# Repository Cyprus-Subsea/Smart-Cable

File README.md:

# Smart-Cable
Smart Cable is a cable assembly with a modular pressure tolerant electronics circuit embedded inline a cable assembly. It was deigned to be able to take care of most sensor integration needs such as voltage regulation, protocol translation, data processing, storage and many more which usually requires many months of engineering effort. The circuit consists of a base plate with the right connections to connect any variation of modules. the modules consist of processor module, protocol modules (RS-323, 485, 422, Ethernet, USB, CAN-bus) , power module and a variety of miscellaneous modules (ADC, memory, Real-time clock, etc.)

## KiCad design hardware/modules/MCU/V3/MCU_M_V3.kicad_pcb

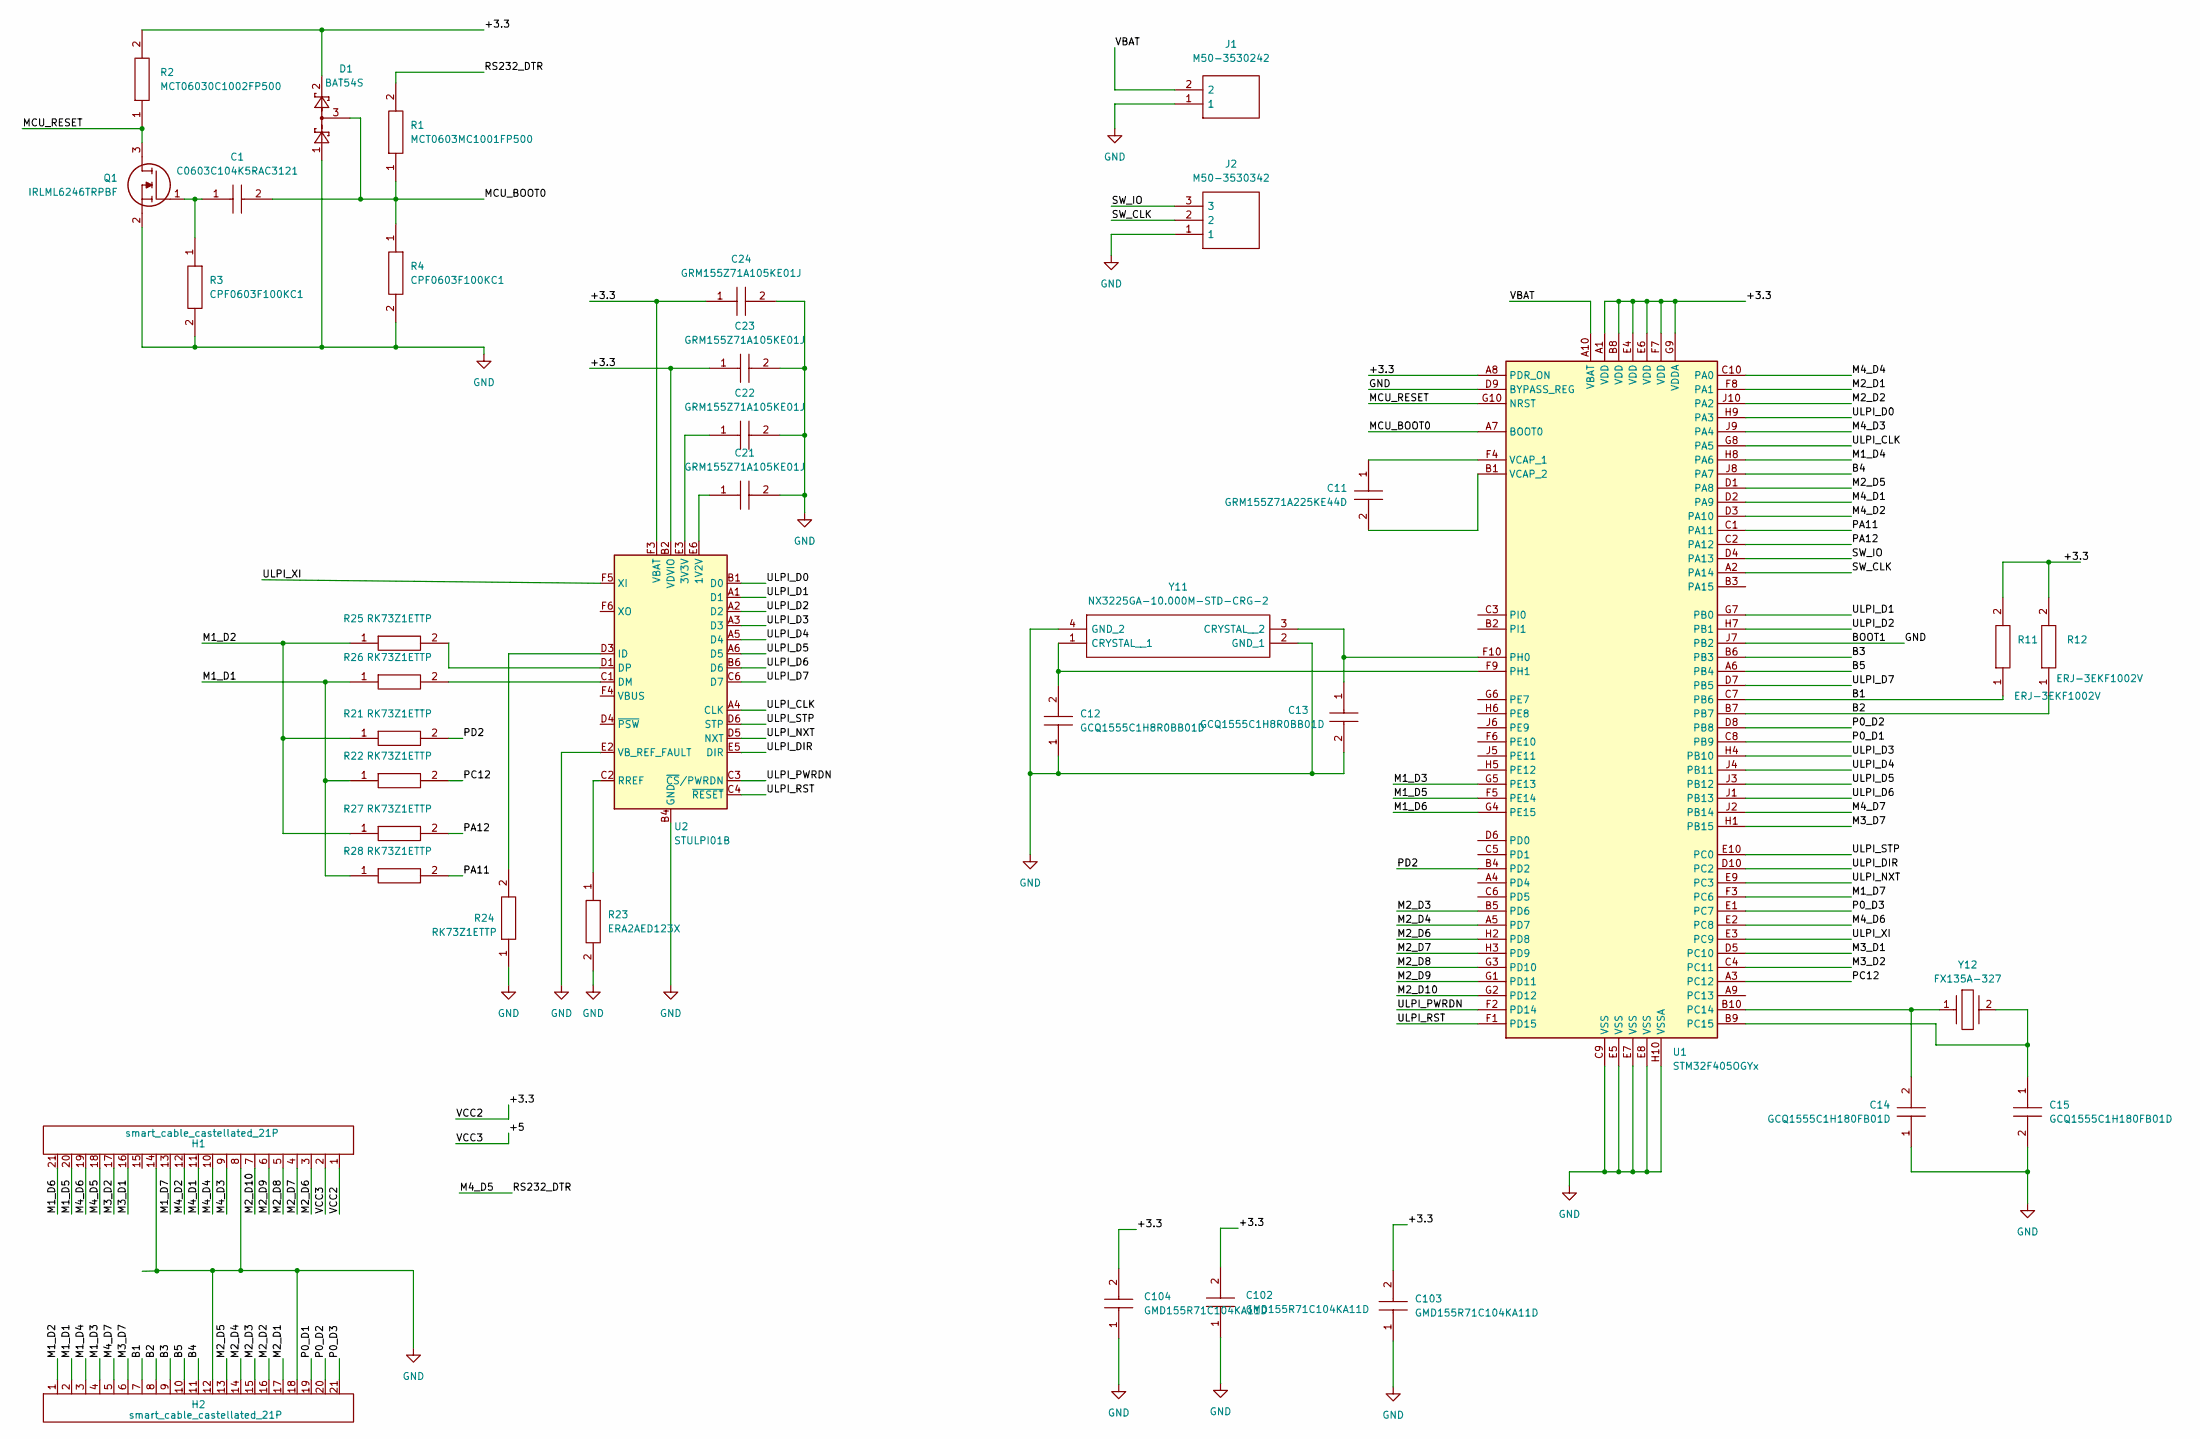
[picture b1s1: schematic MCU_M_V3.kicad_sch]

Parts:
C1: C0603C104K5RAC3121; CAPC1608X95N; Manufacturer_Part_Number C0603C104K5RAC3121; Mouser Part Number 80-C603C104K5RAC3121
C11: GRM155Z71A225KE44D; CAPC1005X55N; Manufacturer_Part_Number GRM155Z71A225KE44D; Mouser Part Number 81-GRM155Z71A225KE4D
C12, C13: GCQ1555C1H8R0BB01D; CAPC1005X55N; Manufacturer_Part_Number GCQ1555C1H8R0BB01D; Mouser Part Number 81-GCQ1555C1H8R0BB1D
C14, C15: GCQ1555C1H180FB01D; CAPC1005X55N; Manufacturer_Part_Number GCQ1555C1H180FB01D; Mouser Part Number 81-GCQ1555C1H180FB1D
C21, C22, C23, C24: GRM155Z71A105KE01J; CAPC1005X55N; Manufacturer_Part_Number GRM155Z71A105KE01J; Mouser Part Number 81-GRM155Z71A105KE1J
C102, C103, C104: GMD155R71C104KA11D; CAPC1005X55N; Manufacturer_Part_Number GMD155R71C104KA11D; Mouser Part Number 81-GMD155R71C104KA1D
D1: BAT54S; SOT-23
H1, H2: smart_cable_castellated_21P; smart_cable_castellated_21p
J1: M50-3530242; HDRV2W40P0X127_1X2_254X210X420P; Manufacturer_Part_Number M50-3530242; Mouser Part Number 855-M50-3530242
J2: M50-3530342; HDRV3W40P0X127_1X3_381X210X430P; Manufacturer_Part_Number M50-3530342; Mouser Part Number 855-M50-3530342
Q1: IRLML6246TRPBF; SOT95P237X112-3N; Manufacturer_Part_Number IRLML6246TRPBF; Mouser Part Number 942-IRLML6246TRPBF
R1: MCT0603MC1001FP500; RESC1608X55N; Manufacturer_Part_Number MCT0603MC1001FP500; Mouser Part Number 594-MCT0603MC1001FP5
R2: MCT06030C1002FP500; RESC1608X55N; Manufacturer_Part_Number MCT06030C1002FP500; Mouser Part Number 594-MCT06030C1002FP5
R3, R4: CPF0603F100KC1; RESC1608X55N; Manufacturer_Part_Number CPF0603F100KC1; Mouser Part Number 279-CPF0603F100KC1
R11, R12: ERJ-3EKF1002V; ERJ3EK_(0603); Manufacturer_Part_Number ERJ-3EKF1002V; Mouser Part Number 667-ERJ-3EKF1002V
R21, R22, R24, R25, R26, R27, R28: RK73Z1ETTP; RESC1005X40N; Manufacturer_Part_Number RK73Z1ETTP; Mouser Part Number 660-RK73Z1ETTP
R23: ERA2AED123X; ERA2AED122X; Manufacturer_Part_Number ERA2AED123X
U1: STM32F405OGYx; ST_WLCSP-90_Die413
U2: STULPI01B; ST_uTFBGA-36_3.6x3.6mm_Layout6x6_P0.5mm
Y11: NX3225GA-10.000M-STD-CRG-2; NX3225GA10000MSTDCRG2; Manufacturer_Part_Number NX3225GA-10.000M-STD-CRG-2; Mouser Part Number 344-NX3225GA10MSTRG2
Y12: FX135A-327; FX135A327; Manufacturer_Part_Number FX135A-327

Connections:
/+3.3: C23.1, C24.1, C102.2, C103.2, C104.2, D1.2, H1.1, R2.2, R11.2, R12.2, U1.A1 (VDD), U1.A8 (PDR_ON), U1.B8 (VDD), U1.E4 (VDD), U1.E6 (VDD), U1.F7 (VDD), U1.G9 (VDDA), U2.B2 (VDVIO), U2.B3 (VDVIO), U2.B5 (VDVIO), U2.F3 (VBAT)
/+5: H1.2
/B1: H2.7, R11.1, U1.C7 (PB6)
/B2: H2.8, R12.1, U1.B7
/B3: H2.9, U1.B6 (PB3)
/B4: H2.11, U1.J8 (PA7)
/B5: H2.10, U1.A6 (PB4)
/M1_D1: H2.2, R22.1, R26.1, R28.1
/M1_D2: H2.1, R21.1, R25.1, R27.1
/M1_D3: H2.4, U1.G5 (PE13)
/M1_D4: H2.3, U1.H8 (PA6)
/M1_D5: H1.20, U1.F5 (PE14)
/M1_D6: H1.21, U1.G4 (PE15)
/M1_D7: H1.13, U1.F3 (PC6)
/M2_D1: H2.17, U1.F8 (PA1)
/M2_D2: H2.16, U1.J10 (PA2)
/M2_D3: H2.15, U1.B5 (PD6)
/M2_D4: H2.14, U1.A5 (PD7)
/M2_D5: H2.13, U1.D1 (PA8)
/M2_D6: H1.3, U1.H2 (PD8)
/M2_D7: H1.4, U1.H3 (PD9)
/M2_D8: H1.5, U1.G3 (PD10)
/M2_D9: H1.6, U1.G1 (PD11)
/M2_D10: H1.7, U1.G2 (PD12)
/M3_D1: H1.16, U1.D5 (PC10)
/M3_D2: H1.17, U1.C4 (PC11)
/M3_D7: H2.6, U1.H1 (PB15)
/M4_D1: H1.11, U1.D2 (PA9)
/M4_D2: H1.12, U1.D3 (PA10)
/M4_D3: H1.9, U1.J9 (PA4)
/M4_D4: H1.10, U1.C10 (PA0)
/M4_D5: H1.18, R1.2
/M4_D6: H1.19, U1.E2 (PC8)
/M4_D7: H2.5, U1.J2 (PB14)
/MCU_BOOT0: C1.2, D1.3, R1.1, R4.1, U1.A7 (BOOT0)
/MCU_RESET: Q1.3, R2.1, U1.G10 (NRST)
/P0_D1: H2.19, U1.C8 (PB9)
/P0_D2: H2.20, U1.D8 (PB8)
/P0_D3: H2.21, U1.E1 (PC7)
/PA11: R28.2, U1.C1 (PA11)
/PA12: R27.2, U1.C2 (PA12)
/PC12: R22.2, U1.A3 (PC12)
/PD2: R21.2, U1.B4 (PD2)
/SW_CLK: J2.2, U1.A2 (PA14)
/SW_IO: J2.3, U1.D4 (PA13)
/ULPI_CLK: U1.G8 (PA5), U2.A4 (CLK)
/ULPI_D0: U1.H9 (PA3), U2.B1 (D0)
/ULPI_D1: U1.G7 (PB0), U2.A1 (D1)
/ULPI_D2: U1.H7 (PB1), U2.A2 (D2)
/ULPI_D3: U1.H4 (PB10), U2.A3 (D3)
/ULPI_D4: U1.J4 (PB11), U2.A5 (D4)
/ULPI_D5: U1.J3 (PB12), U2.A6 (D5)
/ULPI_D6: U1.J1 (PB13), U2.B6 (D6)
/ULPI_D7: U1.D7 (PB5), U2.C6 (D7)
/ULPI_DIR: U1.D10 (PC2), U2.E5 (DIR)
/ULPI_NXT: U1.E9 (PC3), U2.D5 (NXT)
/ULPI_PWRDN: U1.F2 (PD14), U2.C3 (~CS/PWRDN)
/ULPI_RST: U1.F1 (PD15), U2.C4 (~RESET)
/ULPI_STP: U1.E10 (PC0), U2.D6 (STP)
/ULPI_XI: U1.E3 (PC9), U2.F5 (XI)
/VBAT: J1.2, U1.A10 (VBAT)
GND: C12.1, C13.2, C14.1, C15.2, C21.2, C22.2, C23.2, C24.2, C102.1, C103.1, C104.1, D1.1, H1.8, H1.14, H2.12, H2.18, J1.1, J2.1, Q1.2, R3.2, R4.2, R23.2, R24.1, U1.C9 (VSS), U1.D9 (BYPASS_REG), U1.E5 (VSS), U1.E7 (VSS), U1.E8 (VSS), U1.H10 (VSSA), U1.J7 (PB2), U2.B4 (GND), U2.C5 (GND), U2.D2 (GND), U2.E1 (GND), U2.E2 (VB_REF_FAULT), U2.E4 (GND), Y11.2 (GND_1), Y11.4 (GND_2)
unnamed: C1.1, Q1.1, R3.1
unnamed: C11.1, U1.F4 (VCAP_1)
unnamed: C11.2, U1.B1 (VCAP_2)
unnamed: C12.2, U1.F9 (PH1), Y11.1 (CRYSTAL__1)
unnamed: C13.1, U1.F10 (PH0), Y11.3 (CRYSTAL__2)
unnamed: C14.2, U1.B10 (PC14), Y12.1
unnamed: C15.1, U1.B9 (PC15), Y12.2
unnamed: C21.1, U2.E6 (1V2V)
unnamed: C22.1, U2.E3 (3V3V)
unnamed: R23.1, U2.C2 (RREF)
unnamed: R24.2, U2.D3 (ID)
unnamed: R25.2, U2.D1 (DP)
unnamed: R26.2, U2.C1 (DM)

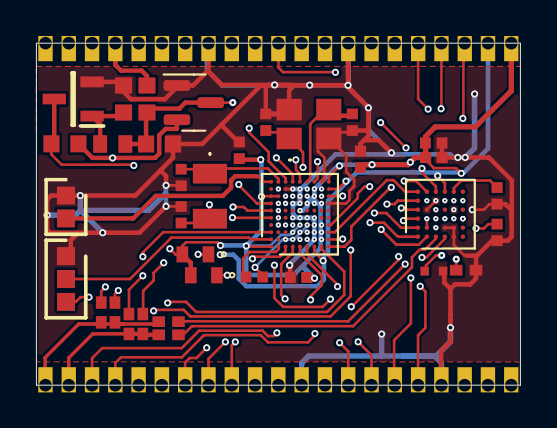
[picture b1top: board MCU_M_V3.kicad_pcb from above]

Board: 4 copper layers, 26.9 x 19.0 mm, 37 parts (0 on the bottom side), 74 nets.

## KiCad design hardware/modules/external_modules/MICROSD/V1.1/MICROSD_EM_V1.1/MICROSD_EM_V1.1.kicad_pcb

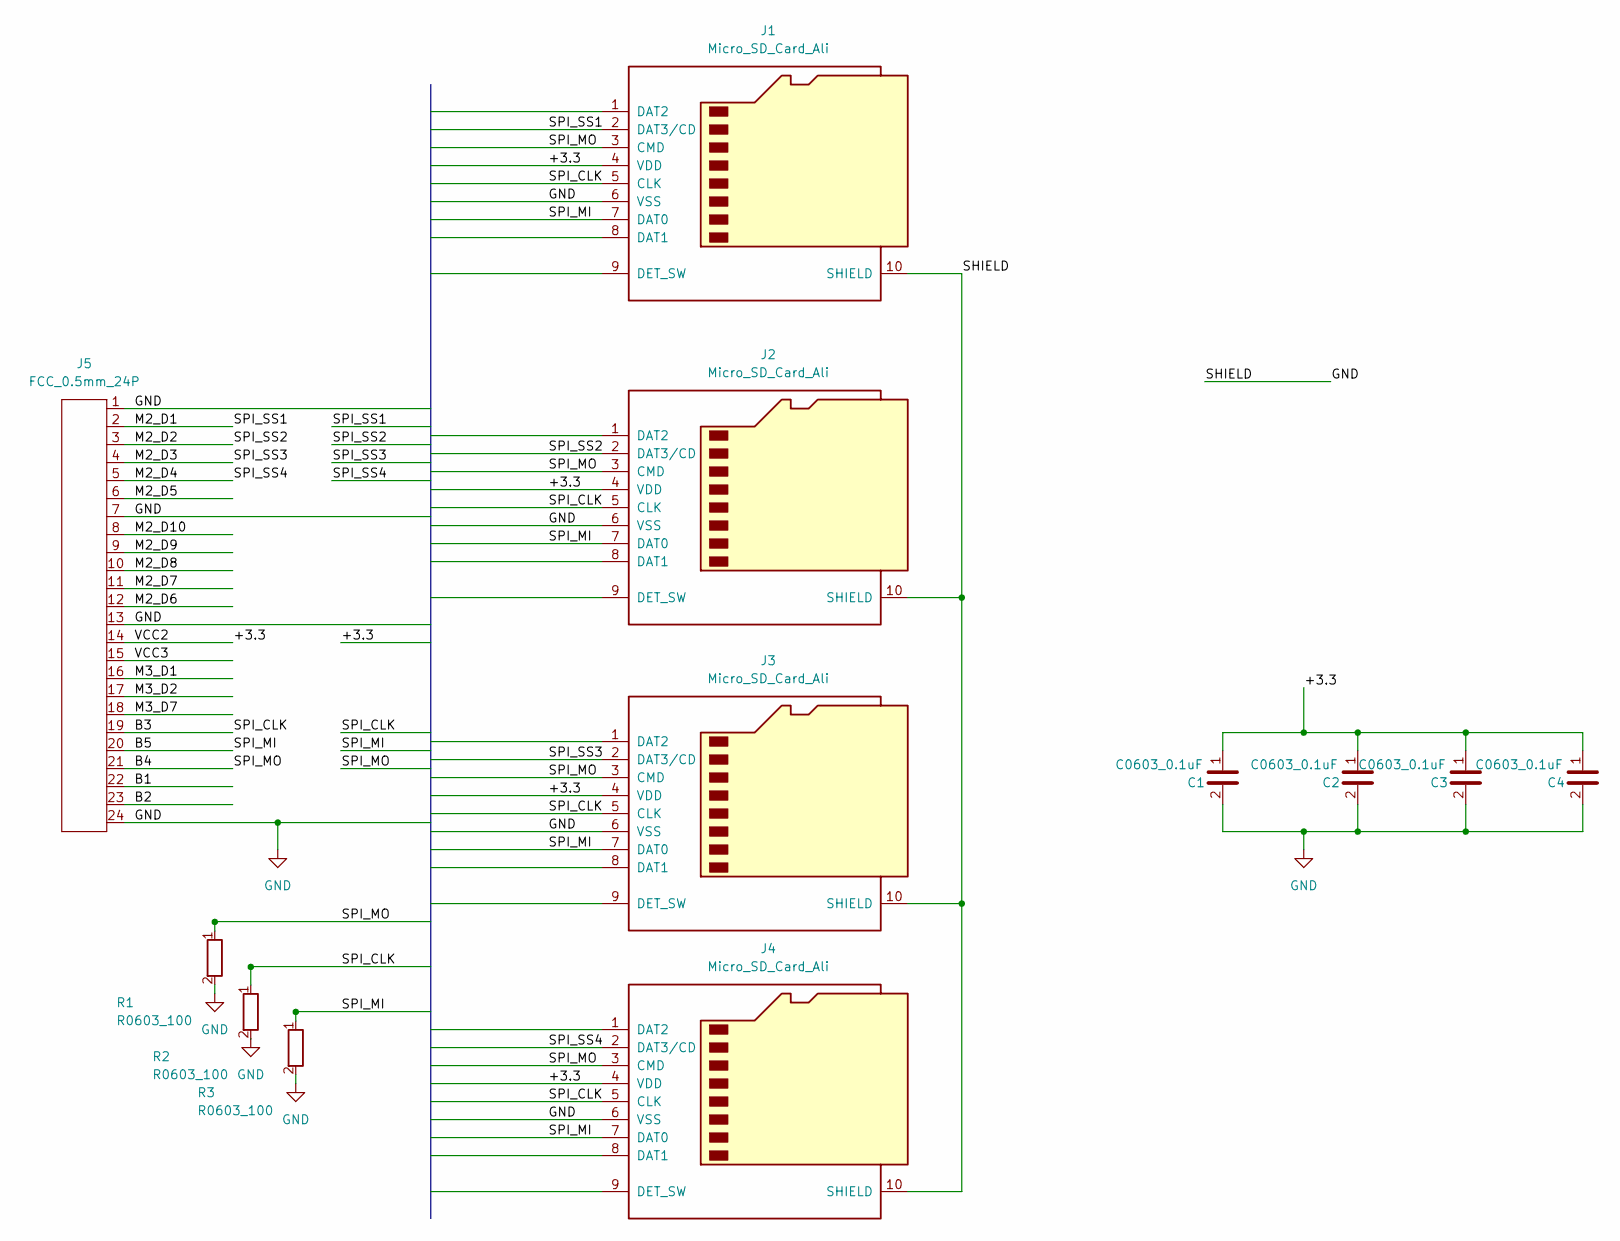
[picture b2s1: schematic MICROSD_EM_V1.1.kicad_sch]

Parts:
C1, C2, C3, C4: C0603_0.1uF; C_0603_1608Metric
J1, J2, J3, J4: Micro_SD_Card_Ali; MicroSD_ALI
J5: FCC_0.5mm_24P; FCC 0.5mm 24P
R1, R2, R3: R0603_100; R_0603_1608Metric

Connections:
/+3.3: C1.1, C2.1, C3.1, C4.1, J1.4 (VDD), J2.4 (VDD), J3.4 (VDD), J4.4 (VDD), J5.14
/B1: J5.22
/B2: J5.23
/B3: J1.5 (CLK), J2.5 (CLK), J3.5 (CLK), J4.5 (CLK), J5.19, R2.1
/B4: J1.3 (CMD), J2.3 (CMD), J3.3 (CMD), J4.3 (CMD), J5.21, R1.1
/B5: J1.7 (DAT0), J2.7 (DAT0), J3.7 (DAT0), J4.7 (DAT0), J5.20, R3.1
/M2_D1: J1.2 (DAT3/CD), J5.2
/M2_D2: J2.2 (DAT3/CD), J5.3
/M2_D3: J3.2 (DAT3/CD), J5.4
/M2_D4: J4.2 (DAT3/CD), J5.5
/M2_D5: J5.6
/M2_D6: J5.12
/M2_D7: J5.11
/M2_D8: J5.10
/M2_D9: J5.9
/M2_D10: J5.8
/M3_D1: J5.16
/M3_D2: J5.17
/M3_D7: J5.18
/VCC3: J5.15
GND: C1.2, C2.2, C3.2, C4.2, J1.6 (VSS), J1.10 (SHIELD), J2.6 (VSS), J2.10 (SHIELD), J3.6 (VSS), J3.10 (SHIELD), J4.6 (VSS), J4.10 (SHIELD), J5.1, J5.7, J5.13, J5.24, R1.2, R2.2, R3.2

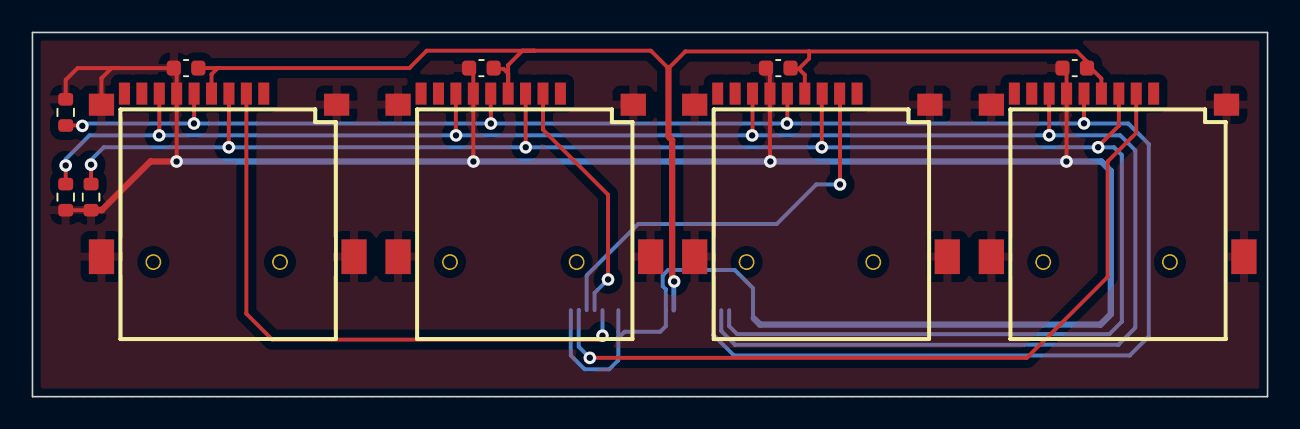
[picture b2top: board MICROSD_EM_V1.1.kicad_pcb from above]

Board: 2 copper layers, 78.0 x 23.0 mm, 12 parts (1 on the bottom side), 9 nets.

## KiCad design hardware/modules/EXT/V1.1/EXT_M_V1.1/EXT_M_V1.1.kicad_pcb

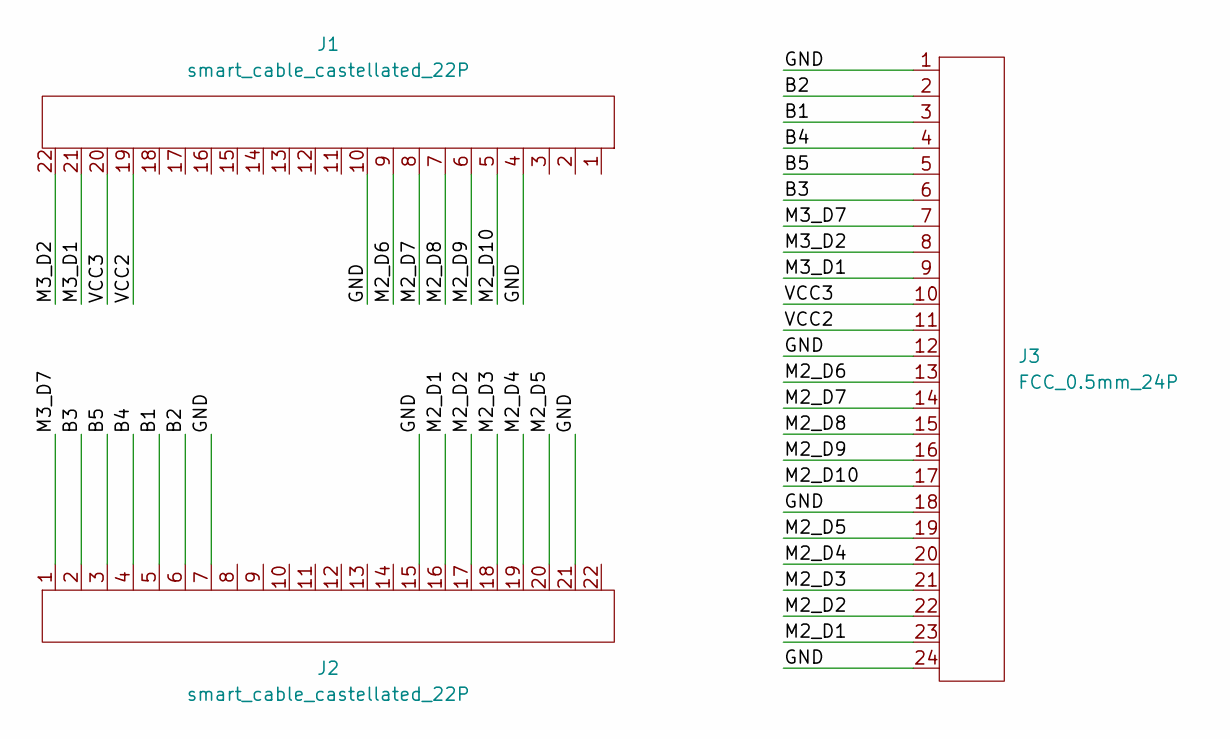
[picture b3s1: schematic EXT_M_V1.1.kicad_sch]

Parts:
J1, J2: smart_cable_castellated_22P; smart_cable_castellated_22p
J3: FCC_0.5mm_24P; FCC 0.5mm 24P

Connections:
/B1: J2.5, J3.3
/B2: J2.6, J3.2
/B3: J2.2, J3.6
/B4: J2.4, J3.4
/B5: J2.3, J3.5
/GND: J1.4, J1.10, J2.7, J2.15, J2.21, J3.1, J3.12, J3.18, J3.24
/M2_D1: J2.16, J3.23
/M2_D2: J2.17, J3.22
/M2_D3: J2.18, J3.21
/M2_D4: J2.19, J3.20
/M2_D5: J2.20, J3.19
/M2_D6: J1.9, J3.13
/M2_D7: J1.8, J3.14
/M2_D8: J1.7, J3.15
/M2_D9: J1.6, J3.16
/M2_D10: J1.5, J3.17
/M3_D1: J1.21, J3.9
/M3_D2: J1.22, J3.8
/M3_D7: J2.1, J3.7
/VCC2: J1.19, J3.11
/VCC3: J1.20, J3.10

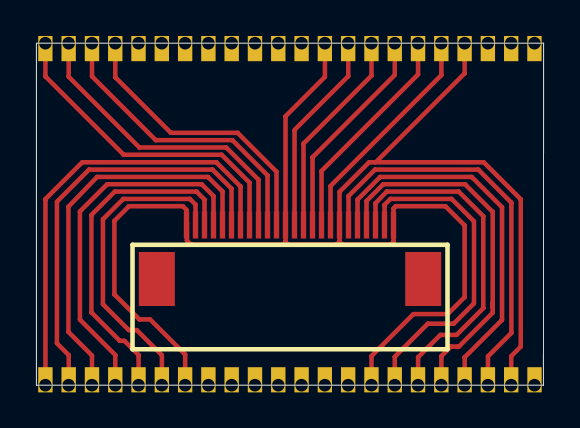
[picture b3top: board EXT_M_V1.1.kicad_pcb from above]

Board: 2 copper layers, 28.2 x 19.0 mm, 3 parts (0 on the bottom side), 21 nets.

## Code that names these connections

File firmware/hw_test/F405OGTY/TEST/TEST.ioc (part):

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Mcu.Name=STM32F405O(E-G)Yx
Mcu.Package=WLCSP90
Mcu.UserName=STM32F405OGYx
PA3.Mode=Host_HS
PA3.Signal=USB_OTG_HS_ULPI_D0
PA5.Mode=Host_HS
PA5.Signal=USB_OTG_HS_ULPI_CK
PB0.Mode=Host_HS
PB0.Signal=USB_OTG_HS_ULPI_D1
PB1.Mode=Host_HS
PB1.Signal=USB_OTG_HS_ULPI_D2
PB10.Mode=Host_HS
PB10.Signal=USB_OTG_HS_ULPI_D3
PB11.Mode=Host_HS
PB11.Signal=USB_OTG_HS_ULPI_D4
PB12.Mode=Host_HS
PB12.Signal=USB_OTG_HS_ULPI_D5
PB13.Mode=Host_HS
PB13.Signal=USB_OTG_HS_ULPI_D6
PB5.Mode=Host_HS
PB5.Signal=USB_OTG_HS_ULPI_D7
PC0.Mode=Host_HS
PC0.Signal=USB_OTG_HS_ULPI_STP
PC2.Mode=Host_HS
PC2.Signal=USB_OTG_HS_ULPI_DIR
PC3.Mode=Host_HS
PC3.Signal=USB_OTG_HS_ULPI_NXT
PC9.Mode=Clock-out-2
PC9.Signal=RCC_MCO_2
PH0-OSC_IN.Mode=HSE-External-Oscillator
PH0-OSC_IN.Signal=RCC_OSC_IN
PH1-OSC_OUT.Mode=HSE-External-Oscillator
PH1-OSC_OUT.Signal=RCC_OSC_OUT
RCC.HSE_VALUE=10000000
RCC.SYSCLKFreq_VALUE=100000000
RCC.SYSCLKSource=RCC_SYSCLKSOURCE_PLLCLK
board=custom

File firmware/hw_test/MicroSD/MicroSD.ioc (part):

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Mcu.Name=STM32F405RGTx
Mcu.Package=LQFP64
Mcu.UserName=STM32F405RGTx
PA1.GPIOParameters=GPIO_Speed,PinState,GPIO_PuPd,GPIO_Label
PA1.GPIO_Label=SS_SD1
PA1.GPIO_PuPd=GPIO_PULLUP
PA1.GPIO_Speed=GPIO_SPEED_FREQ_HIGH
PA1.PinState=GPIO_PIN_SET
PA1.Signal=GPIO_Output
PA10.Mode=Asynchronous
PA10.Signal=USART1_RX
PA11.Mode=Host_Only
PA11.Signal=USB_OTG_FS_DM
PA12.Mode=Host_Only
PA12.Signal=USB_OTG_FS_DP
PA2.GPIOParameters=GPIO_Speed,PinState,GPIO_PuPd,GPIO_Label
PA2.GPIO_Label=SS_SD2
PA2.GPIO_PuPd=GPIO_PULLUP
PA2.GPIO_Speed=GPIO_SPEED_FREQ_HIGH
PA2.PinState=GPIO_PIN_SET
PA2.Signal=GPIO_Output
PA7.GPIOParameters=GPIO_Speed,PinState,GPIO_PuPd,GPIO_Label
PA7.GPIO_Label=SS_SD4
PA7.GPIO_PuPd=GPIO_PULLUP
PA7.GPIO_Speed=GPIO_SPEED_FREQ_HIGH
PA7.PinState=GPIO_PIN_SET
PA7.Signal=GPIO_Output
PA9.Mode=Asynchronous
PA9.Signal=USART1_TX
PB0.GPIOParameters=PinState,GPIO_Label
PB0.GPIO_Label=USB_VBUS
PB0.PinState=GPIO_PIN_SET
PB0.Signal=GPIO_Output
PB3.GPIOParameters=GPIO_PuPd
PB3.GPIO_PuPd=GPIO_PULLUP
PB3.Mode=Full_Duplex_Master
PB3.Signal=SPI1_SCK
PB4.GPIOParameters=GPIO_PuPd
PB4.GPIO_PuPd=GPIO_PULLUP
PB4.Mode=Full_Duplex_Master
PB4.Signal=SPI1_MISO
PB5.GPIOParameters=GPIO_PuPd
PB5.GPIO_PuPd=GPIO_PULLUP
PB5.Mode=Full_Duplex_Master
PB5.Signal=SPI1_MOSI
PC1.GPIOParameters=GPIO_Speed,PinState,GPIO_PuPd,GPIO_Label
PC1.GPIO_Label=SS_SD3
PC1.GPIO_PuPd=GPIO_PULLUP
PC1.GPIO_Speed=GPIO_SPEED_FREQ_HIGH
PC1.PinState=GPIO_PIN_SET
PC1.Signal=GPIO_Output
PC14-OSC32_IN.Mode=LSE-External-Oscillator
PC14-OSC32_IN.Signal=RCC_OSC32_IN
PC15-OSC32_OUT.Mode=LSE-External-Oscillator
PC15-OSC32_OUT.Signal=RCC_OSC32_OUT
PH0-OSC_IN.Mode=HSE-External-Oscillator
PH0-OSC_IN.Signal=RCC_OSC_IN
PH1-OSC_OUT.Mode=HSE-External-Oscillator
PH1-OSC_OUT.Signal=RCC_OSC_OUT
RCC.HSE_VALUE=25000000
RCC.SYSCLKFreq_VALUE=120000000
RCC.SYSCLKSource=RCC_SYSCLKSOURCE_PLLCLK
board=custom

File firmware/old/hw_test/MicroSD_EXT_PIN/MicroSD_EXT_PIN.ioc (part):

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Mcu.Name=STM32F405RGTx
Mcu.Package=LQFP64
Mcu.UserName=STM32F405RGTx
PA1.GPIOParameters=PinState,GPIO_PuPd,GPIO_Label
PA1.GPIO_Label=PIN_PA1
PA1.GPIO_PuPd=GPIO_NOPULL
PA1.PinState=GPIO_PIN_SET
PA1.Signal=GPIO_Output
PA10.Mode=Asynchronous
PA10.Signal=USART1_RX
PA13.Mode=Serial_Wire
PA13.Signal=SYS_JTMS-SWDIO
PA14.Mode=Serial_Wire
PA14.Signal=SYS_JTCK-SWCLK
PA2.GPIOParameters=PinState,GPIO_PuPd,GPIO_Label
PA2.GPIO_Label=PIN_PA2
PA2.GPIO_PuPd=GPIO_NOPULL
PA2.PinState=GPIO_PIN_SET
PA2.Signal=GPIO_Output
PA7.GPIOParameters=PinState,GPIO_PuPd,GPIO_Label
PA7.GPIO_Label=PIN_PA7
PA7.GPIO_PuPd=GPIO_NOPULL
PA7.PinState=GPIO_PIN_SET
PA7.Signal=GPIO_Output
PA9.Mode=Asynchronous
PA9.Signal=USART1_TX
PB3.GPIOParameters=PinState,GPIO_Label
PB3.GPIO_Label=PIN_PB3
PB3.PinState=GPIO_PIN_SET
PB3.Signal=GPIO_Output
PB4.GPIOParameters=PinState,GPIO_Label
PB4.GPIO_Label=PIN_PB4
PB4.PinState=GPIO_PIN_SET
PB4.Signal=GPIO_Output
PB5.GPIOParameters=PinState,GPIO_Label
PB5.GPIO_Label=PIN_PB5
PB5.PinState=GPIO_PIN_SET
PB5.Signal=GPIO_Output
PC1.GPIOParameters=PinState,GPIO_Label
PC1.GPIO_Label=PIN_PC1
PC1.PinState=GPIO_PIN_SET
PC1.Signal=GPIO_Output
PH0-OSC_IN.Mode=HSE-External-Oscillator
PH0-OSC_IN.Signal=RCC_OSC_IN
PH1-OSC_OUT.Mode=HSE-External-Oscillator
PH1-OSC_OUT.Signal=RCC_OSC_OUT
RCC.HSE_VALUE=25000000
RCC.SYSCLKFreq_VALUE=50000000
RCC.SYSCLKSource=RCC_SYSCLKSOURCE_PLLCLK
board=custom

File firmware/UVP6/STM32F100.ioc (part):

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Mcu.Name=STM32F100C(8-B)Tx
Mcu.Package=LQFP48
Mcu.UserName=STM32F100CBTx
PA10.Mode=Asynchronous
PA10.Signal=USART1_RX
PA13.Mode=Serial_Wire
PA13.Signal=SYS_JTMS-SWDIO
PA14.Mode=Serial_Wire
PA14.Signal=SYS_JTCK-SWCLK
PA2.Mode=Asynchronous
PA2.Signal=USART2_TX
PA3.Mode=Asynchronous
PA3.Signal=USART2_RX
PA5.Mode=Full_Duplex_Master
PA5.Signal=SPI1_SCK
PA6.Mode=Full_Duplex_Master
PA6.Signal=SPI1_MISO
PA7.Mode=Full_Duplex_Master
PA7.Signal=SPI1_MOSI
PA9.Mode=Asynchronous
PA9.Signal=USART1_TX
PB0.GPIOParameters=GPIO_Speed,GPIO_Label
PB0.GPIO_Label=SPI1_SS
PB0.GPIO_Speed=GPIO_SPEED_FREQ_HIGH
PB0.Signal=GPIO_Output
PB6.Mode=I2C
PB6.Signal=I2C1_SCL
PB7.Mode=I2C
PB7.Signal=I2C1_SDA
PD0-OSC_IN.Mode=HSE-External-Oscillator
PD0-OSC_IN.Signal=RCC_OSC_IN
PD1-OSC_OUT.Mode=HSE-External-Oscillator
PD1-OSC_OUT.Signal=RCC_OSC_OUT
RCC.HSEDivPLL=RCC_HSE_PREDIV_DIV6
RCC.HSE_VALUE=12000000
RCC.SYSCLKFreq_VALUE=24000000
RCC.SYSCLKSource=RCC_SYSCLKSOURCE_PLLCLK
board=custom

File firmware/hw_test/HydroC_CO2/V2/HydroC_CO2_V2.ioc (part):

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Mcu.Name=STM32F107R(B-C)Tx
Mcu.Package=LQFP64
Mcu.UserName=STM32F107RCTx
PA1.GPIOParameters=GPIO_Speed,PinState,GPIO_Label
PA1.GPIO_Label=SS_SD1
PA1.GPIO_Speed=GPIO_SPEED_FREQ_HIGH
PA1.PinState=GPIO_PIN_SET
PA1.Signal=GPIO_Output
PA10.Mode=Asynchronous
PA10.Signal=USART1_RX
PA11.Mode=Host_Only
PA11.Signal=USB_OTG_FS_DM
PA12.Mode=Host_Only
PA12.Signal=USB_OTG_FS_DP
PA13.Mode=Serial_Wire
PA13.Signal=SYS_JTMS-SWDIO
PA14.Mode=Serial_Wire
PA14.Signal=SYS_JTCK-SWCLK
PA9.Mode=Asynchronous
PA9.Signal=USART1_TX
PB3.Mode=Full_Duplex_Master
PB3.Signal=SPI1_SCK
PB4.Mode=Full_Duplex_Master
PB4.Signal=SPI1_MISO
PB5.Mode=Full_Duplex_Master
PB5.Signal=SPI1_MOSI
PC12.Mode=Asynchronous
PC12.Signal=UART5_TX
PD0-OSC_IN.Mode=HSE-External-Oscillator
PD0-OSC_IN.Signal=RCC_OSC_IN
PD1-OSC_OUT.Mode=HSE-External-Oscillator
PD1-OSC_OUT.Signal=RCC_OSC_OUT
PD2.Mode=Asynchronous
PD2.Signal=UART5_RX
RCC.HSEDivPLL=RCC_HSE_PREDIV_DIV5
RCC.HSE_VALUE=25000000
RCC.SYSCLKFreq_VALUE=48000000
RCC.SYSCLKSource=RCC_SYSCLKSOURCE_PLLCLK
board=custom

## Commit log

2020-10-16 motherboard and modules
2020-10-18 not shown
2020-10-18 motherboard files
2020-10-18 not working
2020-10-18 motherboard upload
2020-10-20 cleaning
2020-10-20 test
2021-01-29 Memory module added
2021-03-01 fw UVP6 HYDROPHONE hw_test added
2021-05-24 UVP_V1
2021-09-30 ADC added
2022-01-09 SPECIFIC ADC_UART_V1 added
2022-03-31 hydroc added
2022-05-12 USB icListen added
2022-05-18 icListen microSD added
2022-05-19 icListen microSD storage added
2022-05-31 icListen USB CDC pre
2022-06-13 icListen commands,flash added
2022-06-15 UI added
2022-06-15 icListen V2 fatfs RW error fixed
2022-06-15 icListen fatfs write block IT
2022-06-21 icListen RTC added
2022-06-21 icListen time epoch added
2022-06-24 icListen storage functions added
2022-07-10 icListen files period added, WAV header fixed
2022-07-10 icListen multidisk fixed
2022-07-10 icListen setup added, flie index added
2022-07-10 icListen bug fixes
2022-08-11 icListe UI bugs fixed
2022-08-27 MCU_V3_SCH added
2022-08-31 MCU_V3 draft added
2022-08-31 MCU_V3 fix1
2022-09-03 MCU_V3 fix2
2022-09-07 MCU_V3 fix3
2022-09-08 MCU_V3 fix4
2023-04-02 UVP3.1 HycroC CO2 CH4
2023-04-11 HydroC UNI
2023-04-12 HydroC UNI minor changes
2023-06-29 sg644_UVP6_added
2024-02-07 slocum G3 added
